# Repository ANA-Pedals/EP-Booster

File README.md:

Built using https://aionfx.com/app/files/schematics/xotic-ep-booster-trace-schematic.png as base.
Designed to fit an 112 x 60 x 31mm enclosure (hopefully).

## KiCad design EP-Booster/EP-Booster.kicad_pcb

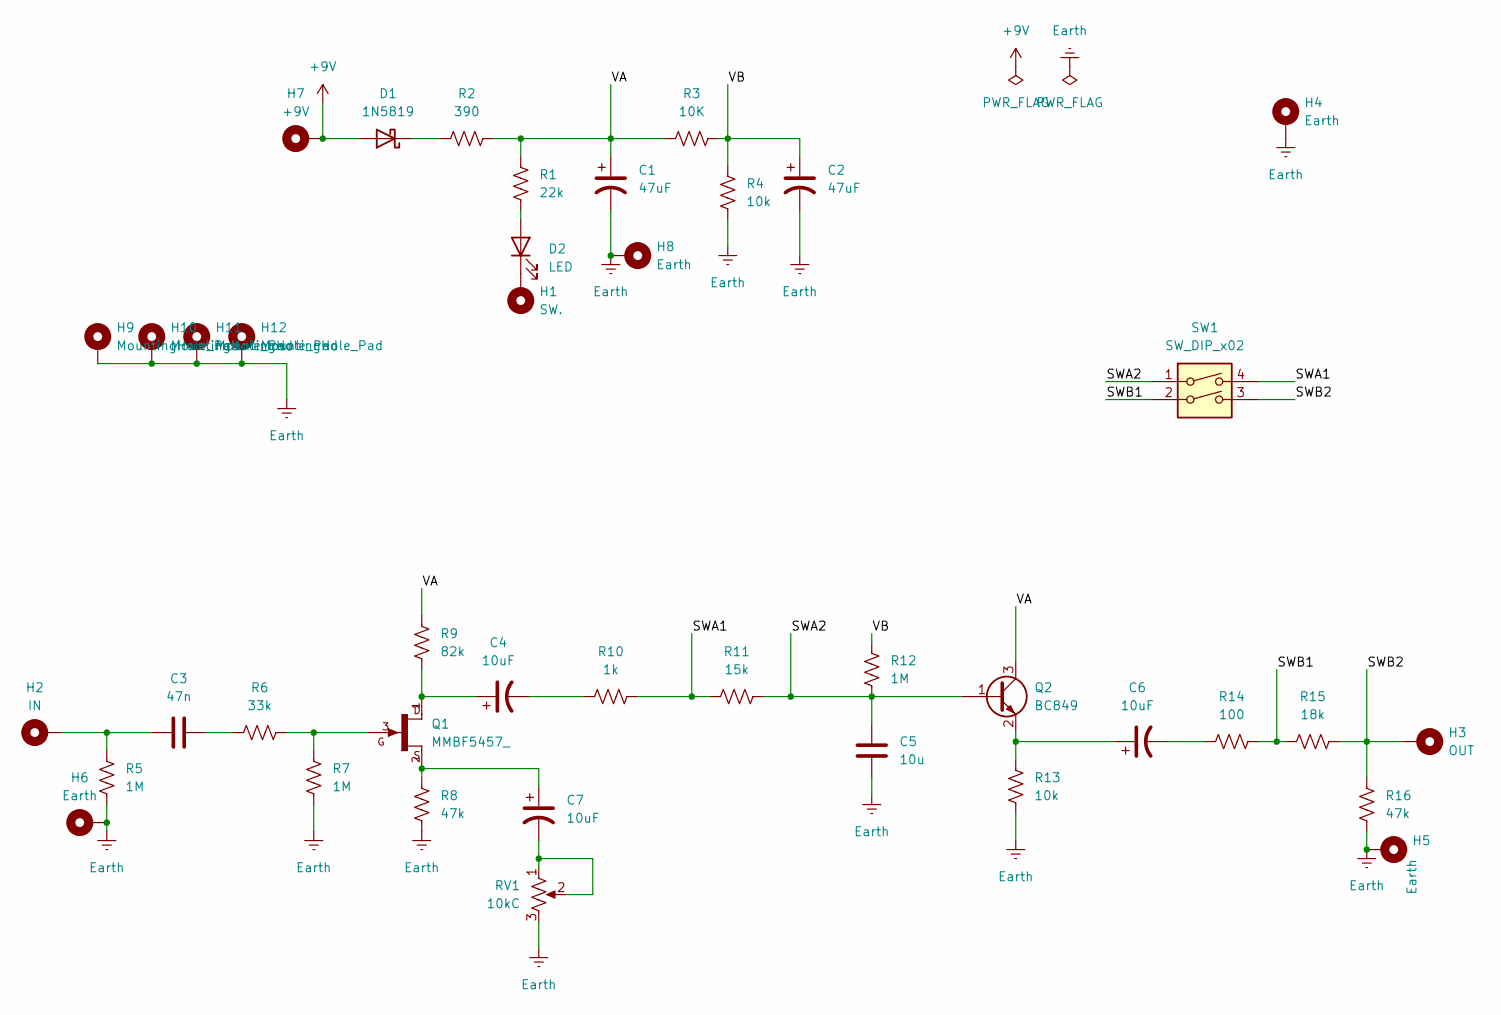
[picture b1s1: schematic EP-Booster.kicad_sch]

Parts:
C1, C2: 47uF; StandardPolarizedCapacitorPedal
C3: 47n; StandardUnpolarizedCapacitorPedal
C4, C6, C7: 10uF; StandardPolarizedCapacitorPedal
C5: 10u; StandardUnpolarizedCapacitorPedal
D1: 1N5819; D_DO-41_SOD81_P10.16mm_Horizontal
D2: LED; StandardDiode1N4000
H1: SW.; 1.5mm_MountingHole
H2: IN; 1.5mm_MountingHole
H3: OUT; 1.5mm_MountingHole
H4, H5, H6, H8: Earth; 1.5mm_MountingHole
H7: +9V; 1.5mm_MountingHole
H9, H10, H11, H12: MountingHole_Pad; MountingHole_2.2mm_M2_DIN965_Pad
Q1: MMBF5457_; SOT23; DigiKey_Part_Number MMBF5457TR-ND
Q2: BC849; SOT-23
R1: 22k; StandardResistorPedal
R2: 390; StandardResistorPedal
R3: 10K; StandardResistorPedal
R4, R13: 10k; StandardResistorPedal
R5, R7, R12: 1M; StandardResistorPedal
R6: 33k; StandardResistorPedal
R8, R16: 47k; StandardResistorPedal
R9: 82k; StandardResistorPedal
R10: 1k; StandardResistorPedal
R11: 15k; StandardResistorPedal
R14: 100; StandardResistorPedal
R15: 18k; StandardResistorPedal
RV1: 10kC; StandardPot
SW1: SW_DIP_x02; SW_DIP_SPSTx02_Slide_6.7x6.64mm_W7.62mm_P2.54mm_LowProfile

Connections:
+9V: D1.2 (A), H7.1
/SWA1: R10.2, R11.1, SW1.4
/SWA2: C5.1, Q2.1 (B), R11.2, R12.2, SW1.1
/SWB1: R14.2, R15.1, SW1.2
/SWB2: H3.1, R15.2, R16.1, SW1.3
/VA: C1.1, Q2.3 (C), R1.1, R2.1, R3.1, R9.1
/VB: C2.1, R3.2, R4.1, R12.1
Earth: C1.2, C2.2, C5.2, H4.1, H5.1, H6.1, H8.1, H9.1, H10.1, H11.1, H12.1, R4.2, R5.2, R7.2, R8.2, R13.2, R16.2, RV1.3
unnamed: C3.1, H2.1, R5.1
unnamed: C3.2, R6.1
unnamed: C4.1, Q1.1, R9.2
unnamed: C4.2, R10.1
unnamed: C6.2, R14.1
unnamed: C7.1, Q1.2, R8.1
unnamed: C7.2, RV1.1, RV1.2
unnamed: D1.1 (K), R2.2
unnamed: D2.2 (A), R1.2
unnamed: D2.1 (K), H1.1
unnamed: Q1.3, R6.2, R7.1
unnamed: C6.1, Q2.2 (E), R13.1

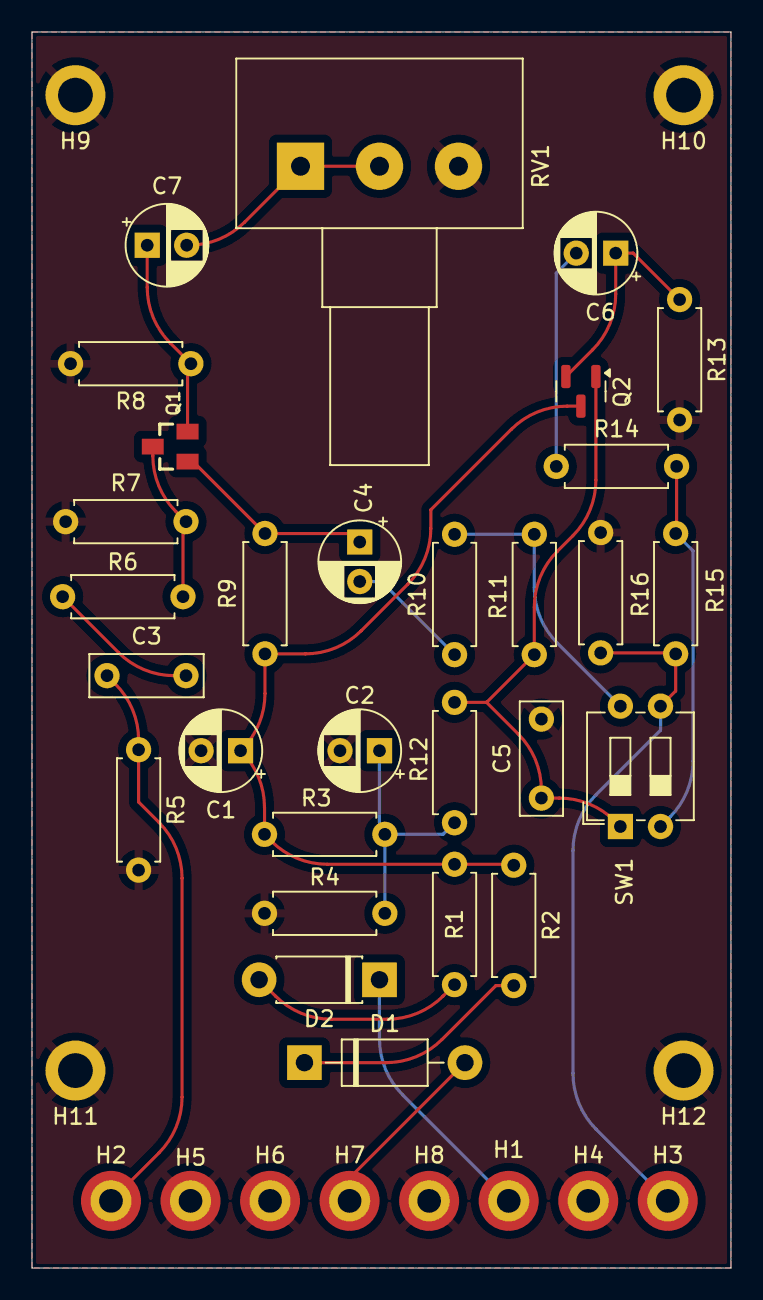
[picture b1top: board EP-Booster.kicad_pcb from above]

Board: 2 copper layers, 44.2 x 78.2 mm, 41 parts (0 on the bottom side), 20 nets.

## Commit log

2025-01-18 added kicad sch
2025-01-23 Finished Schemetic
2025-01-29 first proto
2025-01-30 Revision 1
2025-01-31 Added gerber
2025-04-03 V2.0
